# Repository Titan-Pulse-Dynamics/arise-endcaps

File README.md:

# ARISE End Cap PCBs
================================

This repository contains the End Cap PCBs for ARISE.

ARISE End Cap PCBs are derived from the OreSat End Cap PCBs developed by Portland State Aerospace Society.

Original project:
https://github.com/oresat/oresat-endcaps

Original license:
CERN Open Hardware Licence Version 2 – Strongly Reciprocal
(CERN-OHL-S v2)

See the project history and upstream branch for provenance.

TPD modifications are identified in CHANGELOG.md and the relevant files and documentation.

# "End Cap" PCBs for OreSat

These are the "end cap" PCBs that attach to the +Z and -Z ends of the satellites. Mostly these are to protect the end cards from "space", as well as to hold the magnetometers (two per end cap) as far as away from ferrous stuff as possible. It's also a good place for backup antennas, specifically patch antennas (S band and GPS L1).

## Features

- Cutouts for deployable antennas
- Double magnetometers.
- Single vertical 10mm tall 1.27 mm connector that plugs into the "end card" card.
    - On the End Cap:  Harwin M55-6001242R 12 pin female vertical connector 
    - On the End Card below: Harwin M55-7011242R 12 pin male vertical connector
- No available RF connectors.

## LICENSE

Copyright the Portland State Aerospace Society, 2024.

This source describes Open Hardware that is licensed under CERN-OHL-S v2, or any later version.

You may redistribute and modify this source and make products using it under the terms of the CERN-OHL-S v2 (https://ohwr.org/cern_ohl_s_v2.txt).

This source is distributed WITHOUT ANY EXPRESS OR IMPLIED WARRANTY, INCLUDING OF MERCHANTABILITY, SATISFACTORY QUALITY AND FITNESS FOR A PARTICULAR PURPOSE. Please see the CERN-OHL-S v2 for applicable conditions.

Source location: <https://github.com/oresat/>

As per CERN-OHL-S v2 section 4, should You produce hardware based on this source, You must where practicable maintain the Source Location visible on the external case of the Gizmo or other products you make using this source.

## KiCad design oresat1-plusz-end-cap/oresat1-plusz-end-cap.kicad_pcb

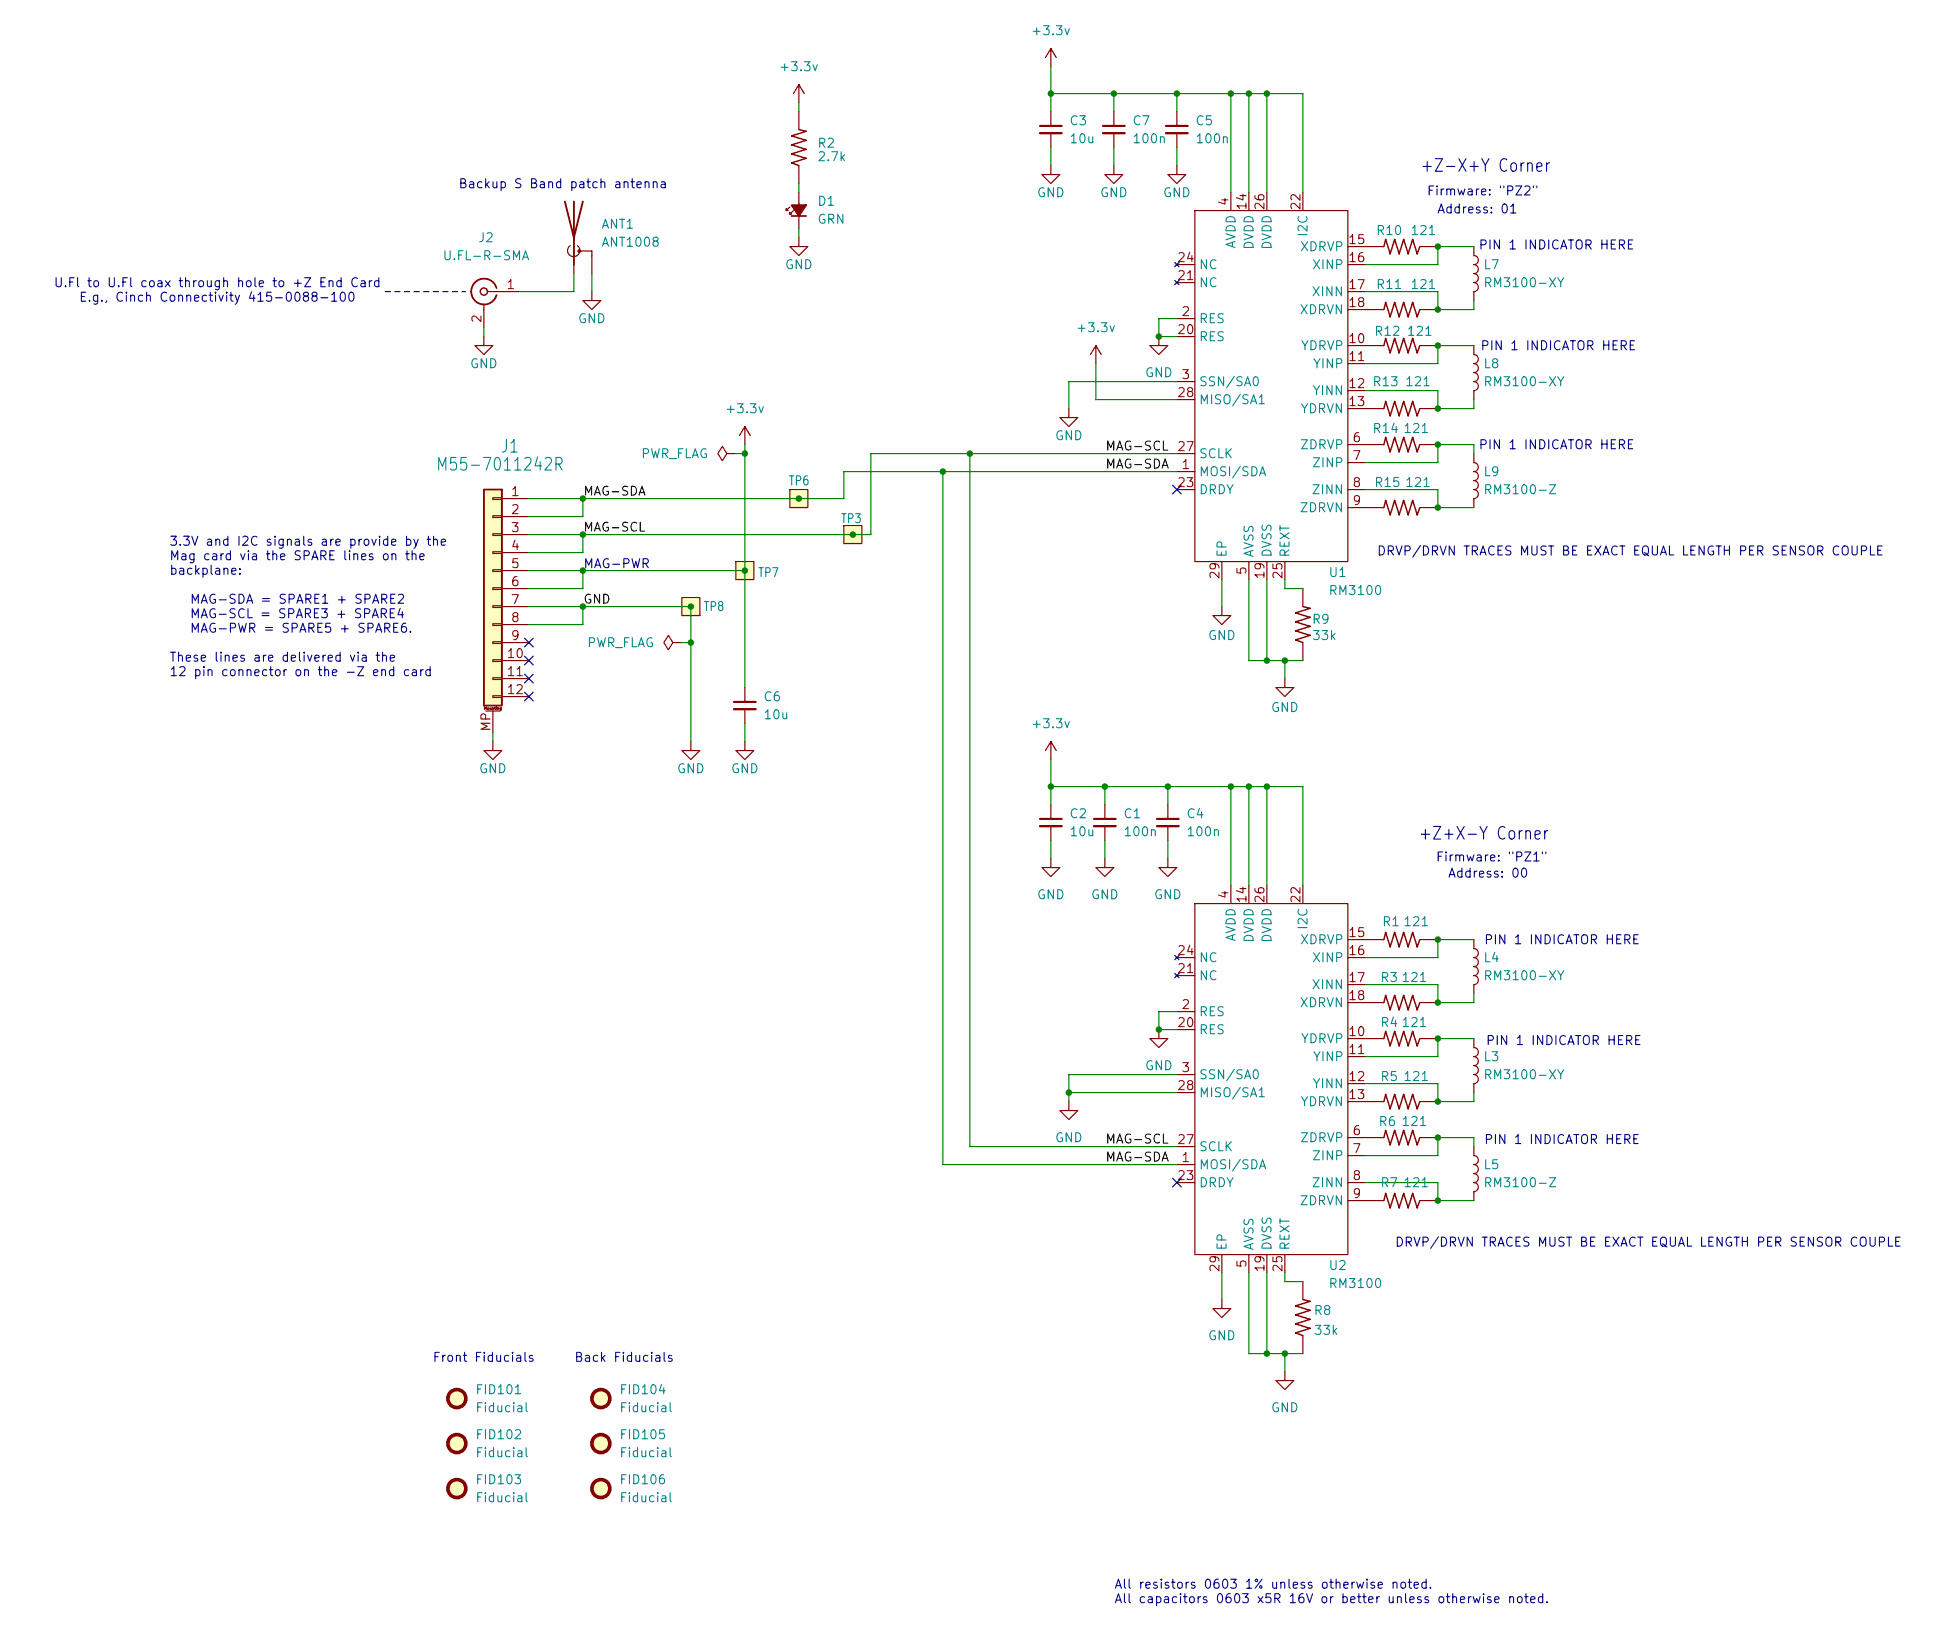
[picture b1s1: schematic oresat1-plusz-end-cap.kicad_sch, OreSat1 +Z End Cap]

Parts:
ANT1: ANT1008; RFMi-ANT1008-S-Band-Patch; MPN ANT1008
C1, C4, C5, C7: 100n; 0603-C-NOSILK; MPN C0603C104K5RACAUTO
C2, C3, C6: 10u; 0805-C-NOSILK; MPN GRT21BC71E106KE13K
D1: GRN; LED_0603_1608Metric; MPN 150060GS75000
FID101, FID102, FID103, FID104, FID105, FID106: Fiducial; Fiducial_1mm_Mask2mm
J1: M55-7011242R; J-Harwin-M55-7XX1242R; MPN M55-7011242R
J2: U.FL-R-SMA; U.FL_Hirose_U.FL-R-SMT-1_Vertical; MPN U.FL-R-SMT-1(10)
L3, L4, L7, L8: RM3100-XY; RM3100 SEN-XY-f; MFR PNI Sensors
L5, L9: RM3100-Z; RM3100 SEN-Z-f; MFR PNI Sensors
R1, R3, R4, R5, R6, R7, R10, R11, R12, R13, R14, R15: 121; 0603-C-NOSILK; MPN RMCF0603FT121R
R2: 2.7k; 0603-C-NOSILK; MPN RMCF0603FT2K70
R8, R9: 33k; 0603-C-NOSILK; MPN RMCF0603FT33K0
TP3, TP6, TP7, TP8: Test-Point; TestPoint-0.75mm-th; MPN N/A
U1, U2: RM3100; RM3100-MagI2C; MFR PNI Sensors

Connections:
+3.3v: C1.1, C2.1, C3.1, C4.1, C5.1, C6.1, C7.1, J1.5, J1.6, R2.2, TP7.1 (1_1), U1.4 (AVDD), U1.14 (DVDD), U1.22 (I2C), U1.26 (DVDD), U1.28 (MISO/SA1), U2.4 (AVDD), U2.14 (DVDD), U2.22 (I2C), U2.26 (DVDD)
/MAG-SCL: J1.3, J1.4, TP3.1 (1_1), U1.27 (SCLK), U2.27 (SCLK)
/MAG-SDA: J1.1, J1.2, TP6.1 (1_1), U1.1 (MOSI/SDA), U2.1 (MOSI/SDA)
GND: ANT1.2 (Shield), C1.2, C2.2, C3.2, C4.2, C5.2, C6.2, C7.2, D1.1 (K), J1.7, J1.8, J1.MP (MountPin), J2.2 (Ext), R8.1, R9.1, TP8.1 (1_1), U1.2 (RES), U1.3 (SSN/SA0), U1.5 (AVSS), U1.19 (DVSS), U1.20 (RES), U1.29 (EP), U2.2 (RES), U2.3 (SSN/SA0), U2.5 (AVSS), U2.19 (DVSS), U2.20 (RES), U2.28 (MISO/SA1), U2.29 (EP)
unnamed: ANT1.1 (A), J2.1 (In)
unnamed: D1.2 (A), R2.1
unnamed: R9.2, U1.25 (REXT)
unnamed: R11.2, U1.18 (XDRVN)
unnamed: R10.2, U1.15 (XDRVP)
unnamed: L7.2, R11.1, U1.17 (XINN)
unnamed: L7.1, R10.1, U1.16 (XINP)
unnamed: R13.2, U1.13 (YDRVN)
unnamed: R12.2, U1.10 (YDRVP)
unnamed: L8.2, R13.1, U1.12 (YINN)
unnamed: L8.1, R12.1, U1.11 (YINP)
unnamed: R15.2, U1.9 (ZDRVN)
unnamed: R14.2, U1.6 (ZDRVP)
unnamed: L9.2, R15.1, U1.8 (ZINN)
unnamed: L9.1, R14.1, U1.7 (ZINP)
unnamed: R8.2, U2.25 (REXT)
unnamed: R3.2, U2.18 (XDRVN)
unnamed: R1.2, U2.15 (XDRVP)
unnamed: L4.2, R3.1, U2.17 (XINN)
unnamed: L4.1, R1.1, U2.16 (XINP)
unnamed: R5.2, U2.13 (YDRVN)
unnamed: R4.2, U2.10 (YDRVP)
unnamed: L3.2, R5.1, U2.12 (YINN)
unnamed: L3.1, R4.1, U2.11 (YINP)
unnamed: R7.2, U2.9 (ZDRVN)
unnamed: R6.2, U2.6 (ZDRVP)
unnamed: L5.2, R7.1, U2.8 (ZINN)
unnamed: L5.1, R6.1, U2.7 (ZINP)

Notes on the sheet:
PIN 1 INDICATOR HERE
Firmware: "PZ2"
DRVP/DRVN TRACES MUST BE EXACT EQUAL LENGTH PER SENSOR COUPLE
+Z-X+Y Corner
U.Fl to U.Fl coax through hole to +Z End Card E.g., Cinch Connectivity 415-0088-100
Front Fiducials
All resistors 0603 1% unless otherwise noted. All capacitors 0603 x5R 16V or better unless otherwise noted.
Address: 01
3.3V and I2C signals are provide by the Mag card via the SPARE lines on the backplane: MAG-SDA = SPARE1 + SPARE2 MAG-SCL = SPARE3 + SPARE4 MAG-PWR = SPARE5 + SPARE6. These lines are delivered via the 12 pin connector on the -Z end card
Back Fiducials
Address: 00
Firmware: "PZ1"
+Z+X-Y Corner
Backup S Band patch antenna
MAG-PWR

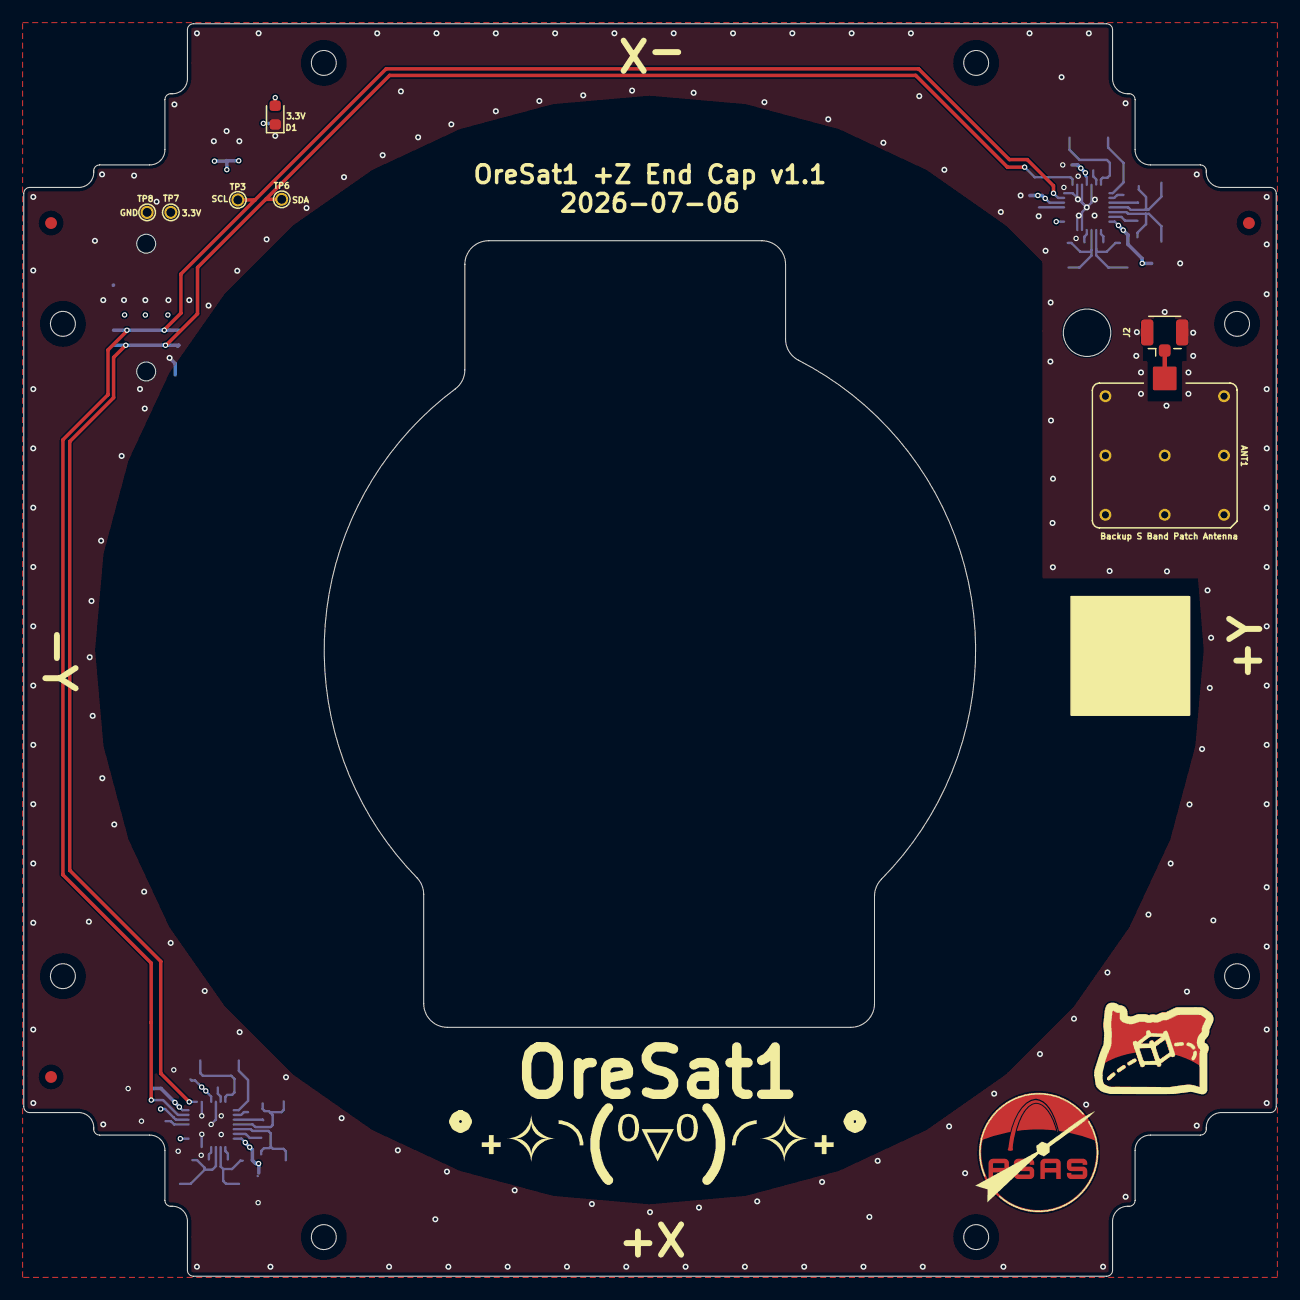
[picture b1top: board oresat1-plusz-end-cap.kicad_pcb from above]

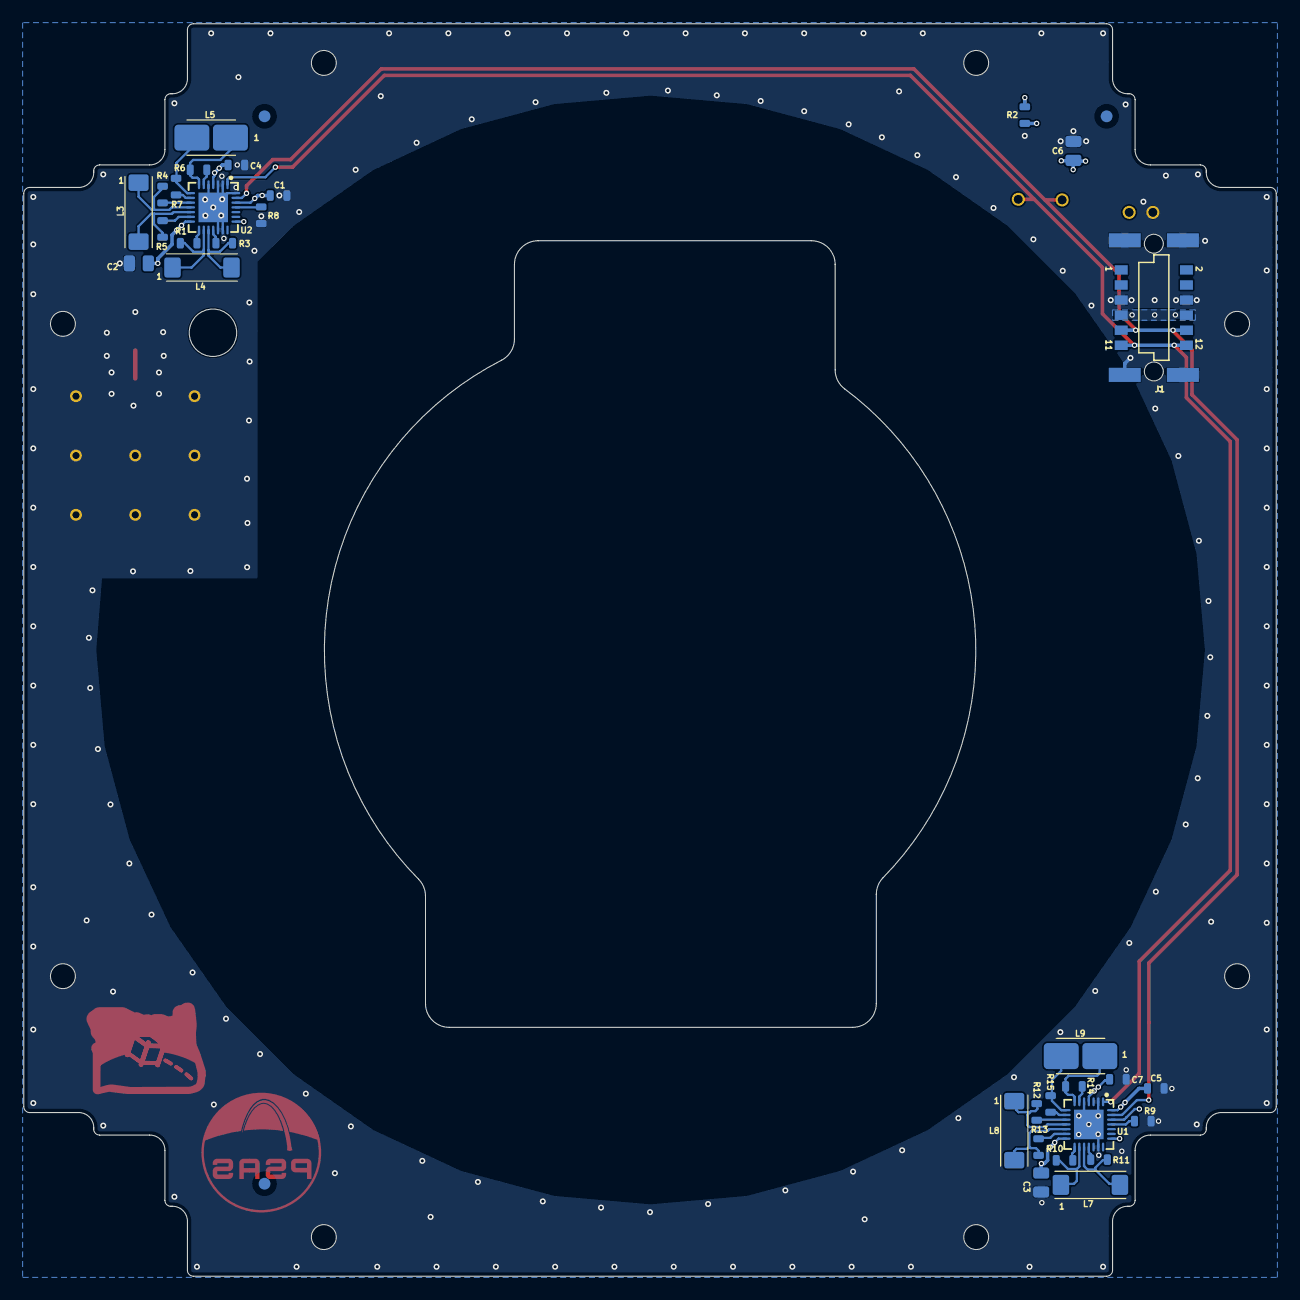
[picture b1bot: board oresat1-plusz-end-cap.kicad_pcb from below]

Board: 4 copper layers, 105.6 x 105.6 mm, 53 parts (34 on the bottom side), 32 nets.

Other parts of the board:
@HOLE4, @HOLE4#2, @HOLE4#3, @HOLE4#4, @HOLE4#5, @HOLE4#6, @HOLE4#7, @HOLE4#8: MountingHole_2.1mm
LOGO1: PSAS_LOGO_10X10
